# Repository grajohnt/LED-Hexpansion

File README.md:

# LED Filament Hexpansion for Tildagon Badge

A very simple hexpansion that takes the 3.3V from the Tildagon badge and adds a resistor and a pot for current-controlled dimming. This allows you to control the brightness of your LED and save battery life on the badge. 

## Usage

There are two large and ornate pads that can accomodate a wide variety of LEDs and LED filaments on both sides of the badge. This means that regardless of the polarity of your filament, you can add it to the front or back and have it be the right way around.

## Components

The pot is a BOURNS 3362P-1-101LF 100 ohm pot, and the resistor is really any old choose-your-wattage 10 ohm resistor. These can of course be varied in value, but this seems to provide a good variety of brightnesses.

## License

MIT License

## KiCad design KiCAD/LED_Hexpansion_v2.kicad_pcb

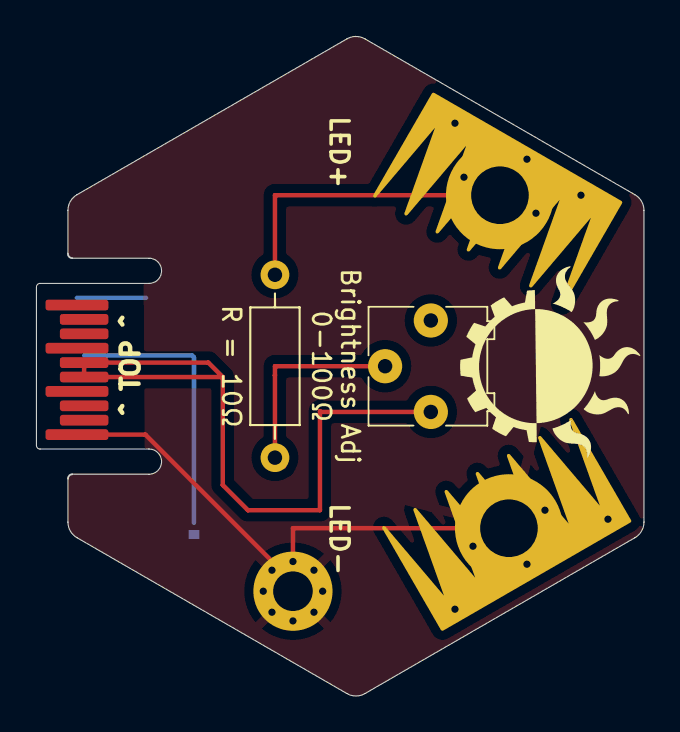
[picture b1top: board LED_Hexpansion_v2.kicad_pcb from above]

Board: 2 copper layers, 33.7 x 36.6 mm, 7 parts (1 on the bottom side), 5 nets.

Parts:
H1: MountingHole_Pad; MountingHole_2.2mm_M2_Pad_Via
H3: LED -; JT_Hexpansion_MountingHole_3.2mm_Pad
H4: LED +; JT_Hexpansion_MountingHole_3.2mm_Pad
J1: Hexpansion-Connector; hexpansion-edge-connector
JP1: SolderJumper_2_Bridged; SolderJumper-2_P1.3mm_Bridged_RoundedPad1.0x1.5mm
R1: Resistor; R_Axial_DIN0207_L6.3mm_D2.5mm_P10.16mm_Horizontal
RV1: potentiometer_3362P

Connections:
/3V3: J1.15 (3V3), J1.16 (3V3), RV1.2
/GND: H1.1, H3.1, J1.1 (GND), J1.10 (GND), J1.11 (GND), J1.14 (GND), J1.17 (GND), J1.20 (GND), JP1.2 (B)
/HEXP_DET: J1.6 (HEXP_DET), JP1.1 (A)
unnamed: H4.1, R1.1
unnamed: R1.2, RV1.1
